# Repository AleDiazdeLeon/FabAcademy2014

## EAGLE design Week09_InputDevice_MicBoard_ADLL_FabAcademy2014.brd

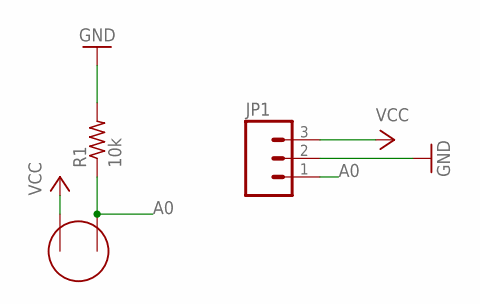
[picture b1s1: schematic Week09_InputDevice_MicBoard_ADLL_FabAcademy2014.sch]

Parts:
JP1: M03PTH; 1X03
R1: 10k; 1206
U$2: ELECTRET; ELECTRET_2742PBJ-A

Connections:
A0: JP1.1, R1.1, U$2.P$1
GND: JP1.2, R1.2
VCC: JP1.3, U$2.P$2

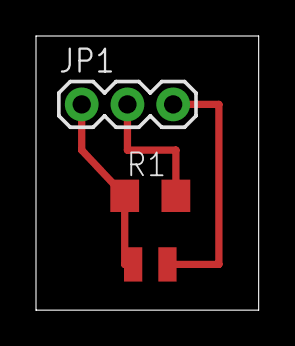
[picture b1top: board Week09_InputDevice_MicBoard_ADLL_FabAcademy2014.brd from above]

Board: 2 copper layers, 12.4 x 15.2 mm, 3 parts (0 on the bottom side), 3 nets.

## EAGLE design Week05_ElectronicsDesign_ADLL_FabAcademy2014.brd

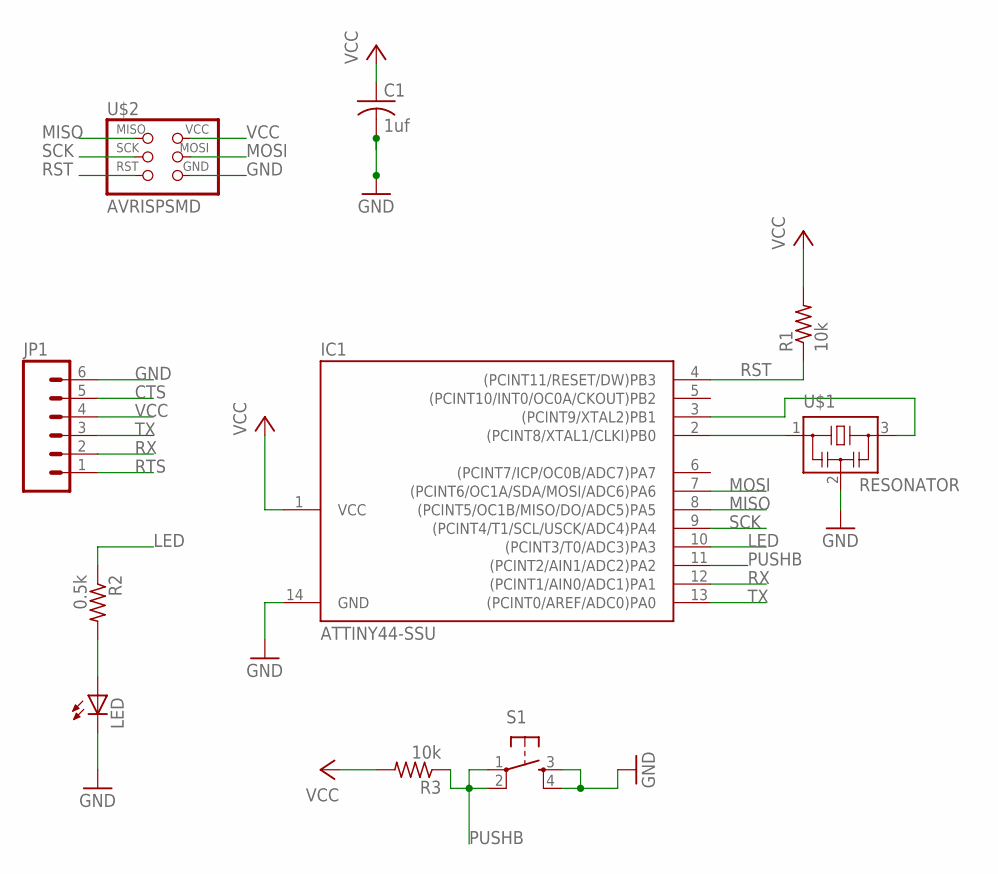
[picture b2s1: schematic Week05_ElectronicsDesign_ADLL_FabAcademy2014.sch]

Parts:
C1: 1uf; C1206
IC1: ATTINY44-SSU; SOIC14
JP1: M06SMD; 1X06-SMD
LED: LED1206; 1206
R1, R3: 10k; R1206
R2: 0.5k; R1206
S1: 6MM_SWITCH6MM_SWITCH; 6MM_SWITCH
U$1: RESONATOR; EFOBM
U$2: AVRISPSMD; 2X03SMD

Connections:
CTS: JP1.5
GND: C1.2, IC1.14 (GND), JP1.6, LED.2 (C), S1.3 (S), S1.4 (S1), U$1.2, U$2.6 (GND)
LED: IC1.10 ((PCINT3/T0/ADC3)PA3), R2.1
MISO: IC1.8 ((PCINT5/OC1B/MISO/DO/ADC5)PA5), U$2.1 (MISO)
MOSI: IC1.7 ((PCINT6/OC1A/SDA/MOSI/ADC6)PA6), U$2.4 (MOSI)
unnamed: IC1.2 ((PCINT8/XTAL1/CLKI)PB0), U$1.1
unnamed: IC1.3 ((PCINT9/XTAL2)PB1), U$1.3
unnamed: LED.1 (A), R2.2
PUSHB: IC1.11 ((PCINT2/AIN1/ADC2)PA2), R3.1, S1.1, S1.2 (P1)
RST: IC1.4 ((PCINT11/RESET/DW)PB3), R1.1, U$2.5 (RST)
RTS: JP1.1
RX: IC1.12 ((PCINT1/AIN0/ADC1)PA1), JP1.2
SCK: IC1.9 ((PCINT4/T1/SCL/USCK/ADC4)PA4), U$2.3 (SCK)
TX: IC1.13 ((PCINT0/AREF/ADC0)PA0), JP1.3
VCC: C1.1, IC1.1 (VCC), JP1.4, R1.2, R3.2, U$2.2 (VCC)

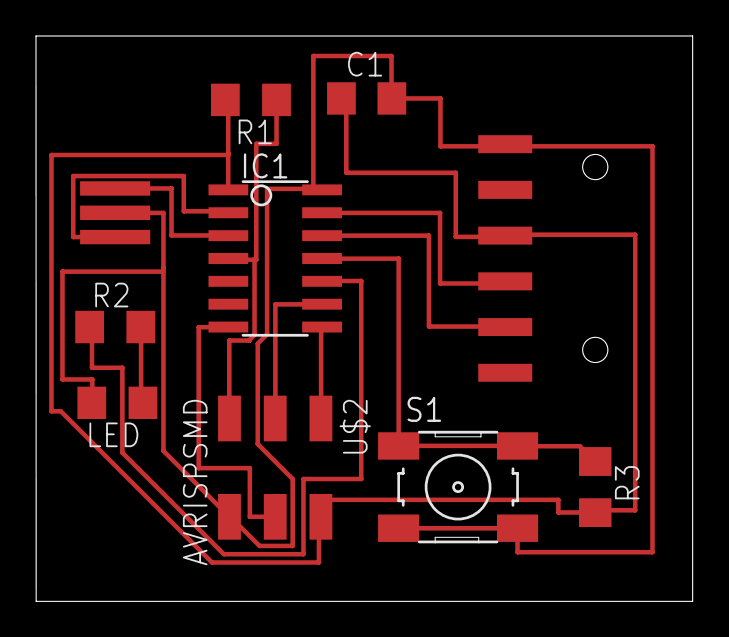
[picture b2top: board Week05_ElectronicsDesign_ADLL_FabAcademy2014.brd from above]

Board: 2 copper layers, 36.5 x 31.4 mm, 10 parts (0 on the bottom side), 13 nets.

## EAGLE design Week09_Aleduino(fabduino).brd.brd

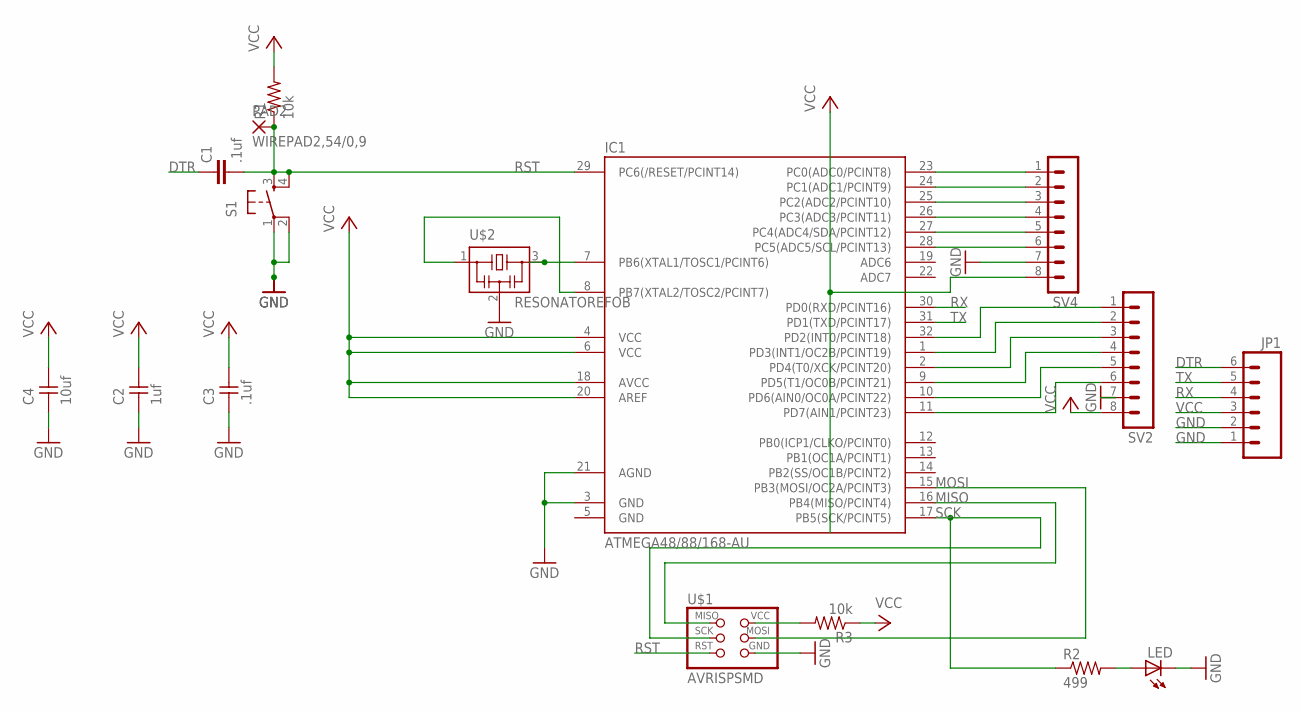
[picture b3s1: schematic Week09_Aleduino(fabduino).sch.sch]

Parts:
C1: .1uf; C1206
C2: 1uf; 1206
C3: .1uf; 1206
C4: 10uf; 1206
IC1: ATMEGA48/88/168-AU; TQFP32-08
JP1: M06SMD; 1X06-SMD
LED: LED1206; 1206
PAD2: WIREPAD2,54/0,9; 2,54/0,9
R1, R3: 10k; 1206
R2: 499; 1206
S1: 6MM_SWITCH6MM_SWITCH; 6MM_SWITCH
SV2, SV4: MA08-1
U$1: AVRISPSMD; 2X03SMD
U$2: RESONATOREFOB; EFOBM

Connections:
DTR: C1.1, JP1.6
GND: C2.1, C3.1, C4.1, IC1.3 (GND), IC1.5 (GND), IC1.21 (AGND), JP1.1, JP1.2, LED.2 (C), S1.1, S1.2 (P1), SV2.7, SV4.7, U$1.6 (GND), U$2.2
MISO: IC1.16 (PB4(MISO/PCINT4)), U$1.1 (MISO)
MOSI: IC1.15 (PB3(MOSI/OC2A/PCINT3)), U$1.4 (MOSI)
unnamed: IC1.8 (PB7(XTAL2/TOSC2/PCINT7)), U$2.1
unnamed: IC1.23 (PC0(ADC0/PCINT8)), SV4.1
unnamed: IC1.24 (PC1(ADC1/PCINT9)), SV4.2
unnamed: IC1.25 (PC2(ADC2/PCINT10)), SV4.3
unnamed: IC1.26 (PC3(ADC3/PCINT11)), SV4.4
unnamed: IC1.27 (PC4(ADC4/SDA/PCINT12)), SV4.5
unnamed: IC1.28 (PC5(ADC5/SCL/PCINT13)), SV4.6
unnamed: IC1.7 (PB6(XTAL1/TOSC1/PCINT6)), U$2.3
unnamed: IC1.32 (PD2(INT0/PCINT18)), SV2.1
unnamed: IC1.1 (PD3(INT1/OC2B/PCINT19)), SV2.2
unnamed: IC1.2 (PD4(T0/XCK/PCINT20)), SV2.3
unnamed: IC1.9 (PD5(T1/OC0B/PCINT21)), SV2.4
unnamed: IC1.10 (PD6(AIN0/OC0A/PCINT22)), SV2.5
unnamed: IC1.11 (PD7(AIN1/PCINT23)), SV2.6
unnamed: R3.2, U$1.2 (VCC)
unnamed: LED.1 (A), R2.2
RST: C1.2, IC1.29 (PC6(/RESET/PCINT14)), PAD2.1, R1.1, S1.3 (S), S1.4 (S1), U$1.5 (RST)
RX: IC1.30 (PD0(RXD/PCINT16)), JP1.4
SCK: IC1.17 (PB5(SCK/PCINT5)), R2.1, U$1.3 (SCK)
TX: IC1.31 (PD1(TXD/PCINT17)), JP1.5
VCC: C2.2, C3.2, C4.2, IC1.4 (VCC), IC1.6 (VCC), IC1.18 (AVCC), IC1.20 (AREF), JP1.3, R1.2, R3.1, SV2.8, SV4.8

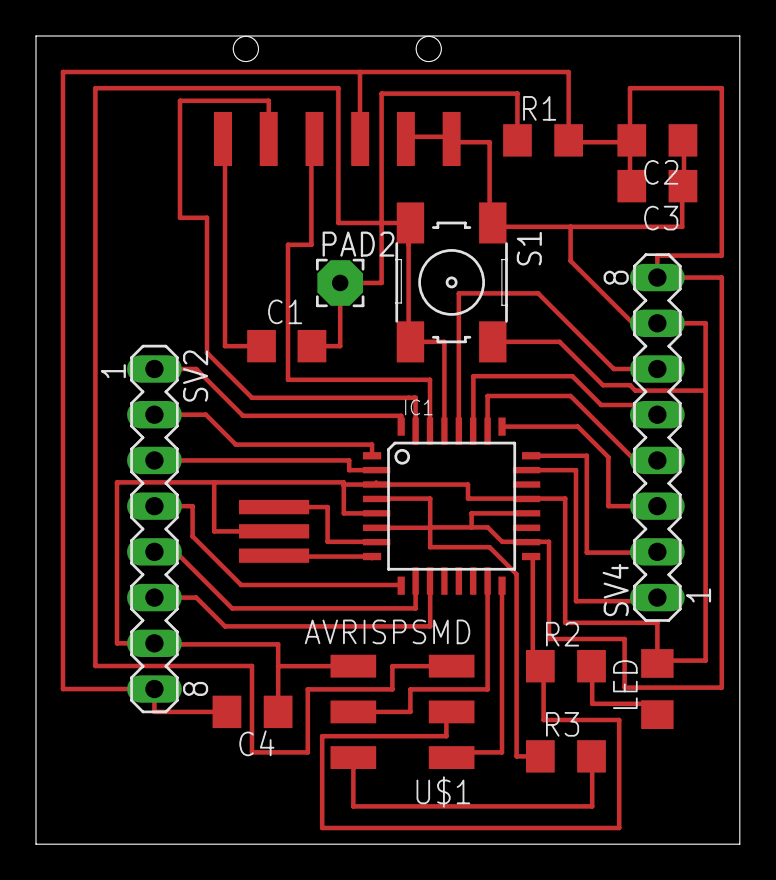
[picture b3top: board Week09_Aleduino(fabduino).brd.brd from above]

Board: 2 copper layers, 39.1 x 44.9 mm, 16 parts (0 on the bottom side), 25 nets.

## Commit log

2014-06-16 Fab Academy 2014 Files
2014-06-16 Files of Weekly Assignments for Fab Academy 2014
2014-06-16 FabAcademy2014 Week Assignments
2014-06-16 FabAcademy2013 Week Asssignmets
2014-06-16 FabAcademy2014 Week Assignment

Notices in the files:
parts and their libraries:
01_SparkFun: Licensing: CC v3.0 Share-Alike You are welcome to use this library for commercial purposes.
